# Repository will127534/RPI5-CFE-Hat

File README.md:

# CFexpress PCIe Hat for Raspberry Pi 5
Welcome to the GitHub repository for the open-source CFexpress (CFE) PCIe Hat designed specifically for the Raspberry Pi 5. This project aims to enhance the Raspberry Pi 5 by adding the ability to interface with CFexpress Type B cards directly, enabling high-speed data transfer and storage solutions.

## Features
* CFexpress Type B Card slot: Directly connect a CFexpress Type B card to your Raspberry Pi 5 for high-speed data storage and transfer.
* Automated Card Mounting: Utilizes a CH32V003 MCU for I2C to GPIO control, enabling the automated mounting and unmounting of the CFexpress card with the press of an eject button.
* QWIIC Hub: Includes a simple QWIIC hub that provides four additional QWIIC ports, allowing for easy expansion and connectivity with other QWIIC-compatible devices.
* Flexible Mounting Options: Designed to be mounted either on the top or the bottom of the Raspberry Pi 5. When mounted on top, the I2C connection is made directly from the GPIO header on the Raspberry Pi 5. For bottom mounting, the QWIIC port is used to connect and enable the auto-mount script.

## Notes
* Automounting feature requires I2C connection from either QWIIC port or RPI GPIO
* The board does not support hot-unplug even with the auto-mount script, so you will need to press the eject button to signal unmount request
* Gerber and CPL file for JLCPCB is under /Gerber
* [Interactive BOM](https://htmlpreview.github.io/?https://github.com/will127534/RPI5-CFE-Hat/blob/main/bom/ibom.html) [(provided by InteractiveHtmlBom)
](https://github.com/openscopeproject/InteractiveHtmlBom) and JLCPCB BOM under /bom
* Source Code for CH32V003 based I2C to GPIO and Python code on RPI under /software
* Limited amount on [Tindle](https://www.tindie.com/products/34094/) for sell

## Support
For questions, issues, or suggestions, please open an issue in the [GitHub repository](https://github.com/will127534/RPI5-CFE-Hat/issues)  
Also see [Quick Start Guide](https://github.com/will127534/RPI5-CFE-Hat/wiki/RPI5-CFE-Hat-Quick-Start-Guide)

## License
This project is licensed under the MIT License - see the LICENSE file for details.

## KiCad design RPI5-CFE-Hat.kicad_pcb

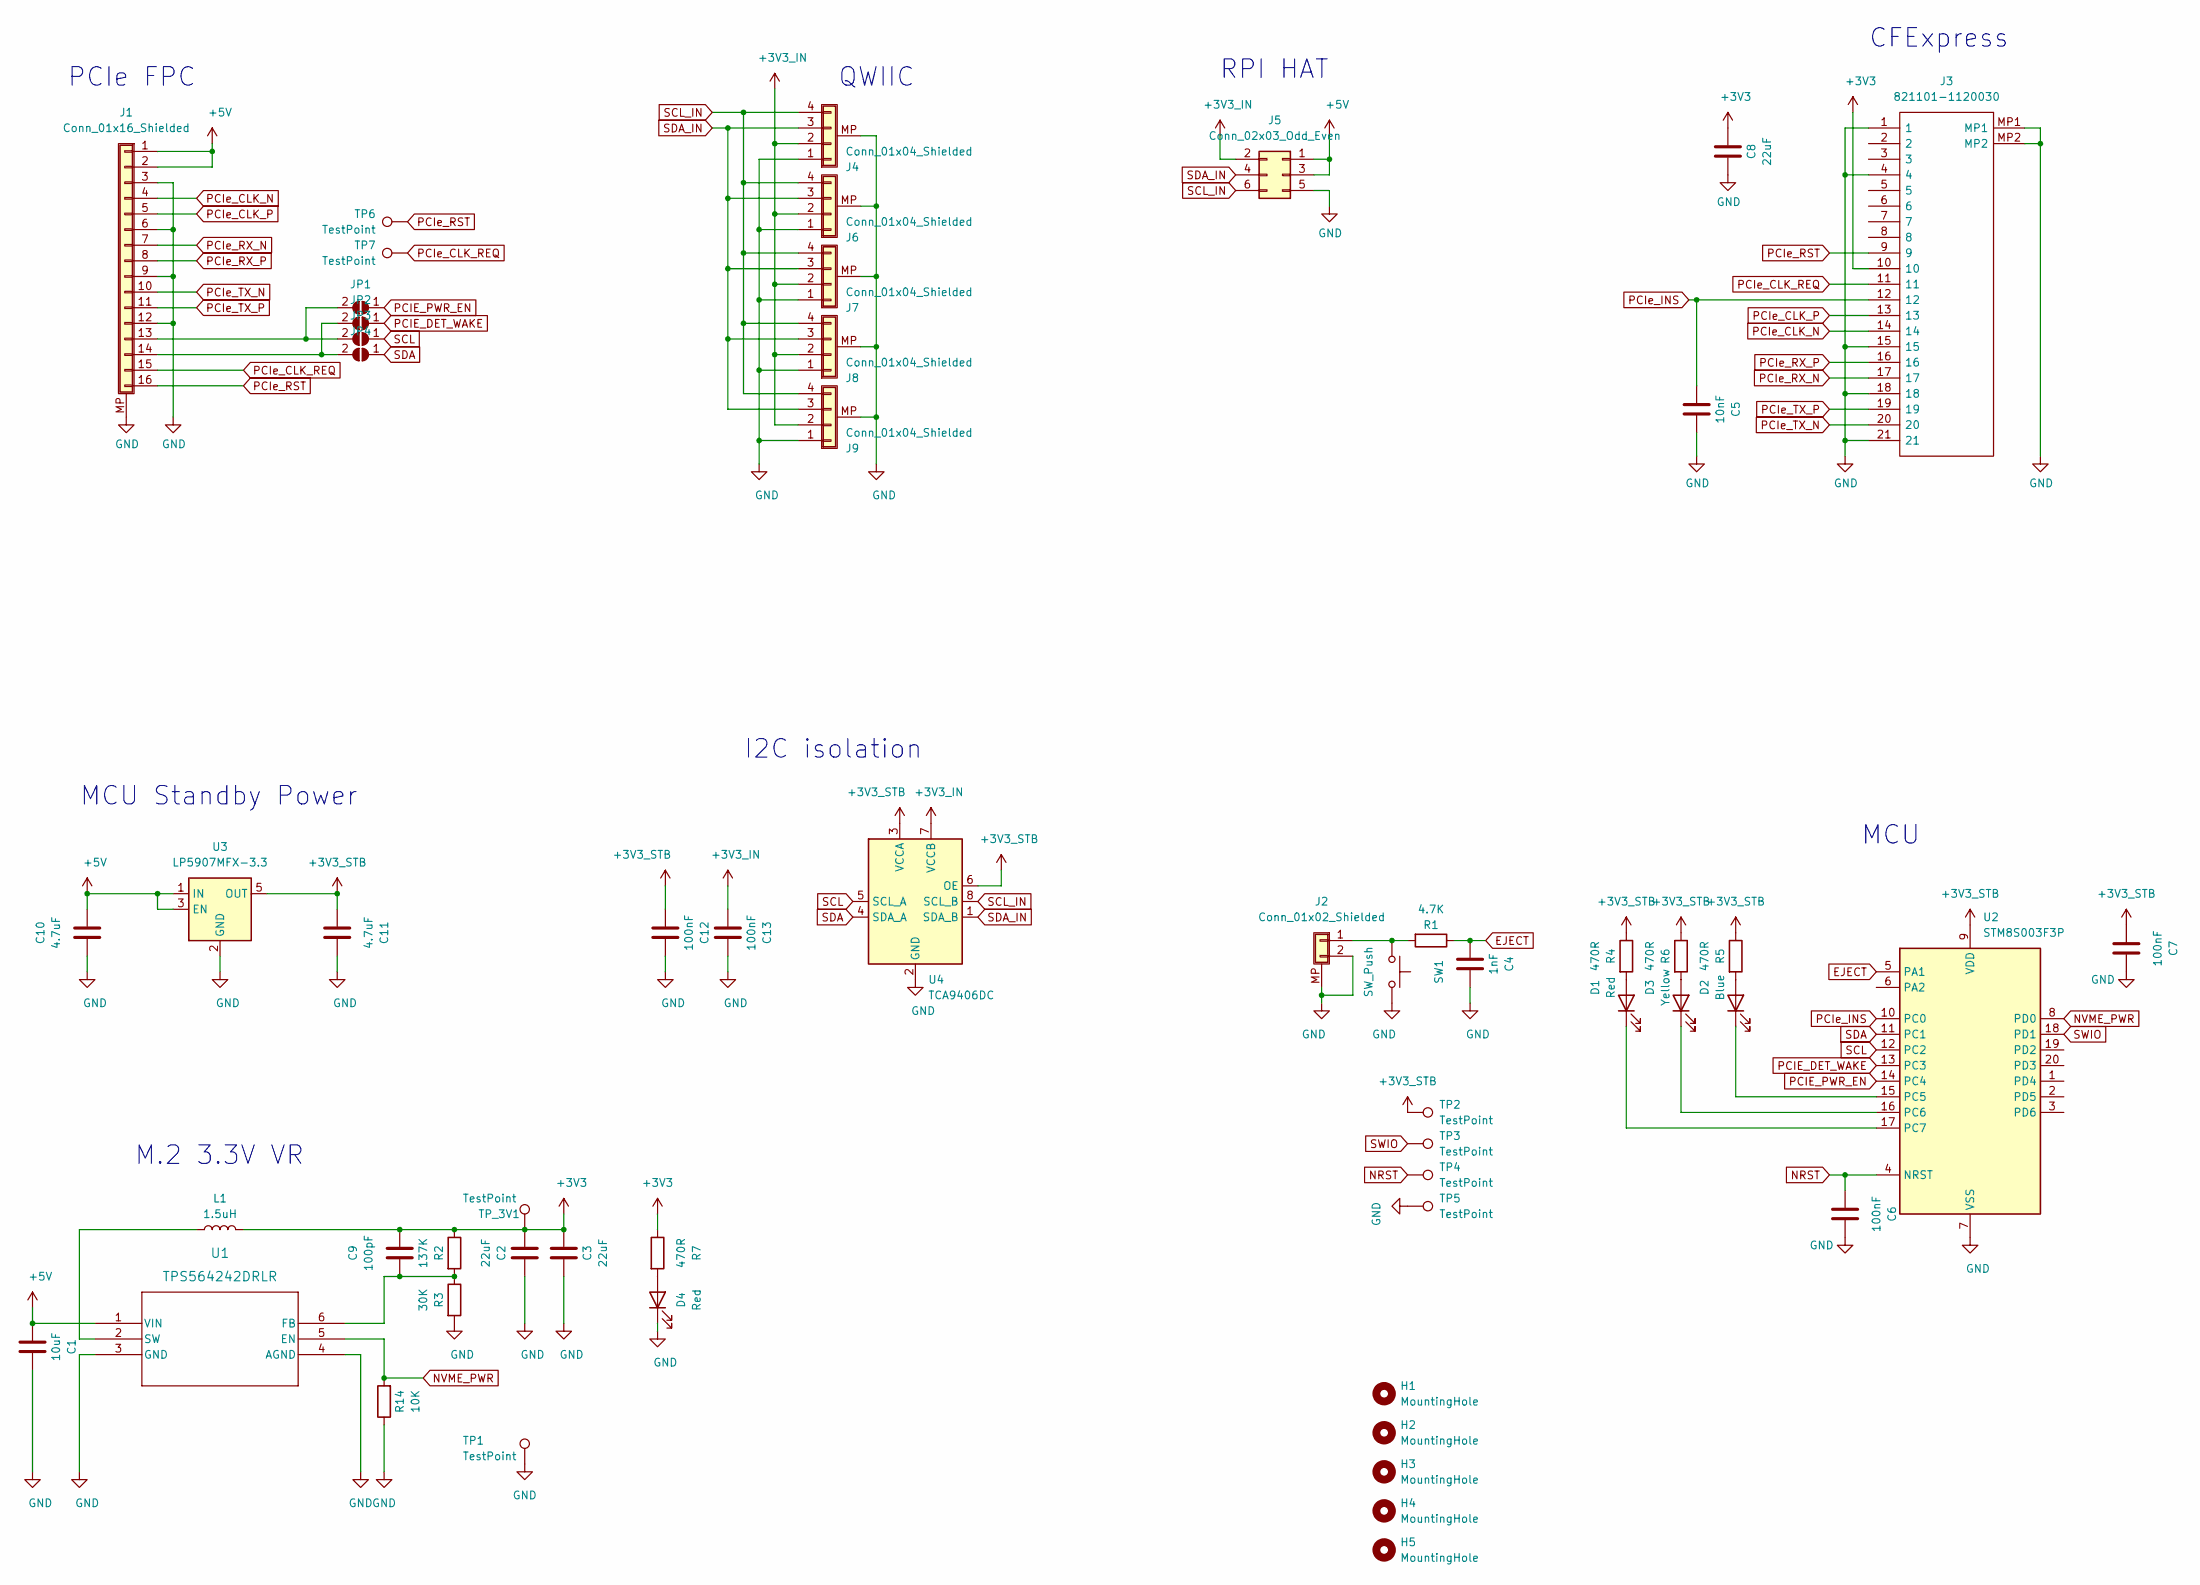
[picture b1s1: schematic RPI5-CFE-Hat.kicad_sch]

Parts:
C1: 10uF; C_0805_2012Metric
C2, C3, C8: 22uF; C_0805_2012Metric
C4: 1nF; C_0402_1005Metric
C5: 10nF; C_0402_1005Metric
C6, C7, C12, C13: 100nF; C_0402_1005Metric
C9: 100pF; C_0402_1005Metric
C10, C11: 4.7uF; C_0603_1608Metric
D1, D4: Red; LED_0603_1608Metric
D2: Blue; LED_0603_1608Metric
D3: Yellow; LED_0603_1608Metric
H1, H2, H3, H4, H5: MountingHole; MountingHole_2.7mm_M2.5
J1: Conn_01x16_Shielded; Hirose_FH12-16S-0.5SH_1x16-1MP_P0.50mm_Horizontal
J2: Conn_01x02_Shielded; JST_SH_SM02B-SRSS-TB_1x02-1MP_P1.00mm_Horizontal
J3: 821101-1120030; 8211011120030; Manufacturer_Part_Number 821101-1120030
J4, J6, J7, J8, J9: Conn_01x04_Shielded; JST_SH_SM04B-SRSS-TB_1x04-1MP_P1.00mm_Horizontal
J5: Conn_02x03_Odd_Even; PinSocket_2x03_P2.54mm_Vertical
JP1, JP2, JP3, JP4: SolderJumper_2_Open; SolderJumper-2_P1.3mm_Open_Pad1.0x1.5mm
L1: 1.5uH; L_Vishay_IHLP-2020
R1: 4.7K; R_0402_1005Metric
R2: 137K; R_0402_1005Metric
R3: 30K; R_0402_1005Metric
R4, R5, R6, R7: 470R; R_0402_1005Metric
R14: 10K; R_0402_1005Metric
SW1: SW_Push; Panasonic_EVQPUM_EVQPUD
TP1, TP2, TP3, TP4, TP5, TP6, TP7: TestPoint; TestPoint_Pad_D1.0mm
TP_3V1: TestPoint; TestPoint_Pad_D1.0mm
U1: TPS564242DRLR; TPS564242DRLR_TEX
U2: STM8S003F3P; TSSOP-20_4.4x6.5mm_P0.65mm
U3: LP5907MFX-3.3; SOT-23-5
U4: TCA9406DC; TCA9406DCUR

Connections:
+3V3: C2.1, C3.2, C8.2, C9.2, J3.10, L1.2, R2.1, R7.1, TP_3V1.1
+3V3_IN: C13.1, J4.2, J5.2, J6.2, J7.2, J8.2, J9.2, U4.7 (VCCB)
+3V3_STB: C7.1, C11.1, C12.1, R4.1, R5.1, R6.1, TP2.1, U2.9 (VDD), U3.5 (OUT), U4.3 (VCCA), U4.6 (OE)
+5V: C1.1, C10.2, J1.1, J1.2, J5.1, J5.3, U1.1 (VIN), U3.1 (IN), U3.3 (EN)
EJECT: C4.1, R1.1, U2.5 (PA1)
GND: C1.2, C2.2, C3.1, C4.2, C5.2, C6.2, C7.2, C8.1, C10.1, C11.2, C12.2, C13.2, D4.1 (K), J1.3, J1.6, J1.9, J1.12, J1.MP (Shield), J2.2, J2.MP (Shield), J3.1, J3.4, J3.15, J3.18, J3.21, J3.MP1, J3.MP2, J4.1, J4.MP (Shield), J5.5, J6.1, J6.MP (Shield), J7.1, J7.MP (Shield), J8.1, J8.MP (Shield), J9.1, J9.MP (Shield), R3.2, R14.1, SW1.1, TP1.1, TP5.1, U1.3 (GND), U1.4 (AGND), U2.7 (VSS), U3.2 (GND), U4.2 (GND)
NRST: C6.1, TP4.1, U2.4 (NRST)
NVME_PWR: R14.2, U1.5 (EN), U2.8 (PD0)
unnamed: C9.1, R2.2, R3.1, U1.6 (FB)
unnamed: D1.1 (K), U2.17 (PC7)
unnamed: D1.2 (A), R4.2
unnamed: D2.1 (K), U2.15 (PC5)
unnamed: D2.2 (A), R5.2
unnamed: D3.1 (K), U2.16 (PC6)
unnamed: D3.2 (A), R6.2
unnamed: D4.2 (A), R7.2
unnamed: J1.13, JP1.2 (B), JP3.2 (B)
unnamed: J1.14, JP2.2 (B), JP4.2 (B)
unnamed: J2.1, R1.2, SW1.2
unnamed: L1.1, U1.2 (SW)
PCIE_DET_WAKE: JP2.1 (A), U2.13 (PC3)
PCIE_PWR_EN: JP1.1 (A), U2.14 (PC4)
PCIe_CLK_N: J1.4, J3.14
PCIe_CLK_P: J1.5, J3.13
PCIe_CLK_REQ: J1.15, J3.11, TP7.1
PCIe_INS: C5.1, J3.12, U2.10 (PC0)
PCIe_RST: J1.16, J3.9, TP6.1
PCIe_RX_N: J1.7, J3.17
PCIe_RX_P: J1.8, J3.16
PCIe_TX_N: J1.10, J3.20
PCIe_TX_P: J1.11, J3.19
SCL: JP3.1 (A), U2.12 (PC2), U4.5 (SCL_A)
SCL_IN: J4.4, J5.6, J6.4, J7.4, J8.4, J9.4, U4.8 (SCL_B)
SDA: JP4.1 (A), U2.11 (PC1), U4.4 (SDA_A)
SDA_IN: J4.3, J5.4, J6.3, J7.3, J8.3, J9.3, U4.1 (SDA_B)
SWIO: TP3.1, U2.18 (PD1)

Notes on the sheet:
MCU
PCIe FPC
MCU Standby Power
QWIIC
I2C isolation
CFExpress
M.2 3.3V VR
RPI HAT

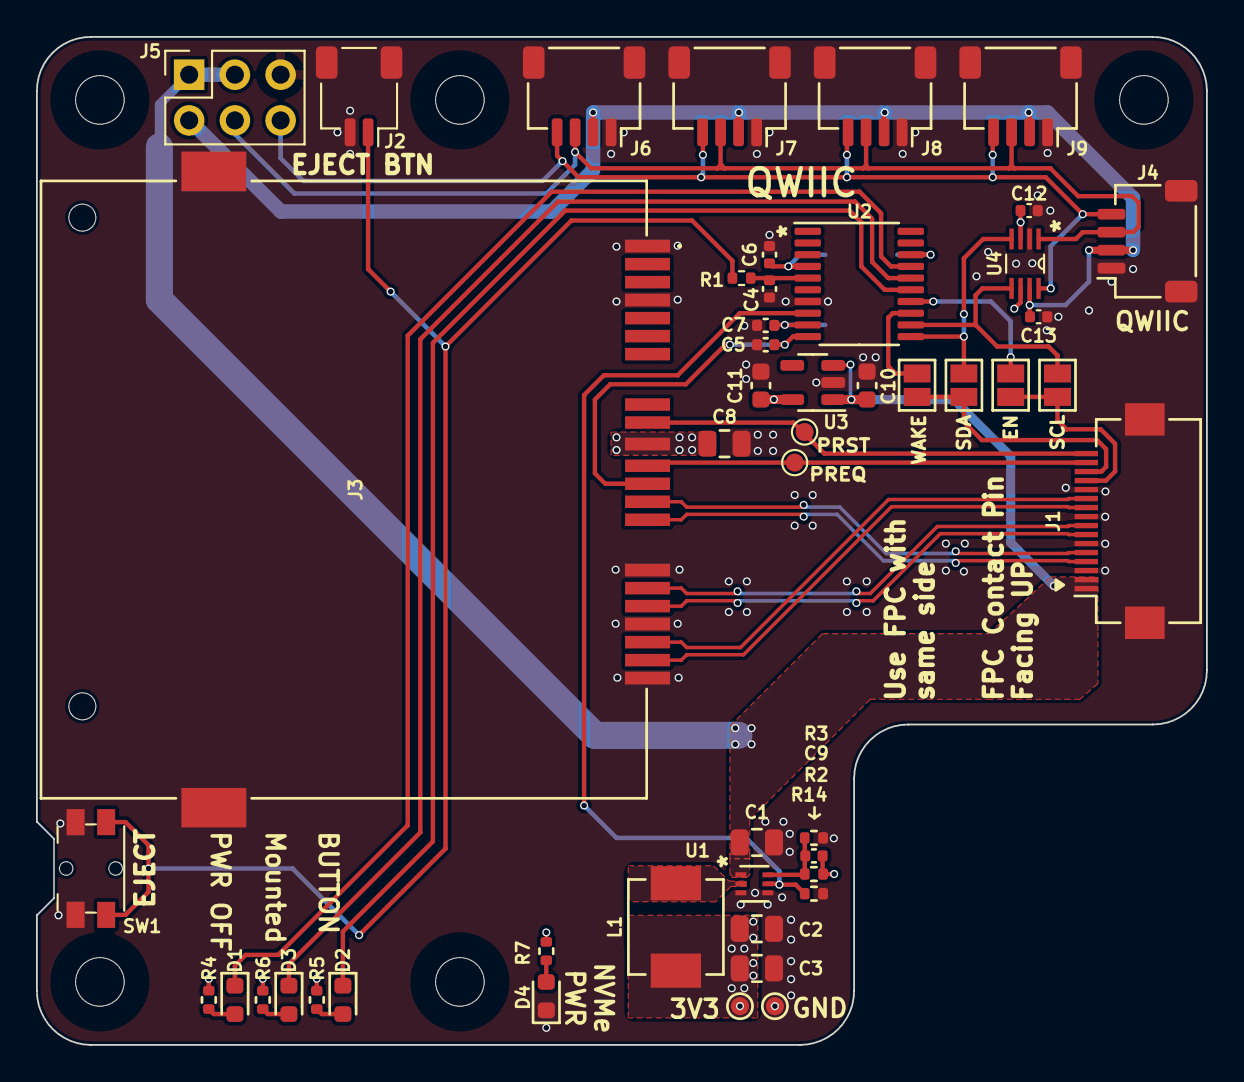
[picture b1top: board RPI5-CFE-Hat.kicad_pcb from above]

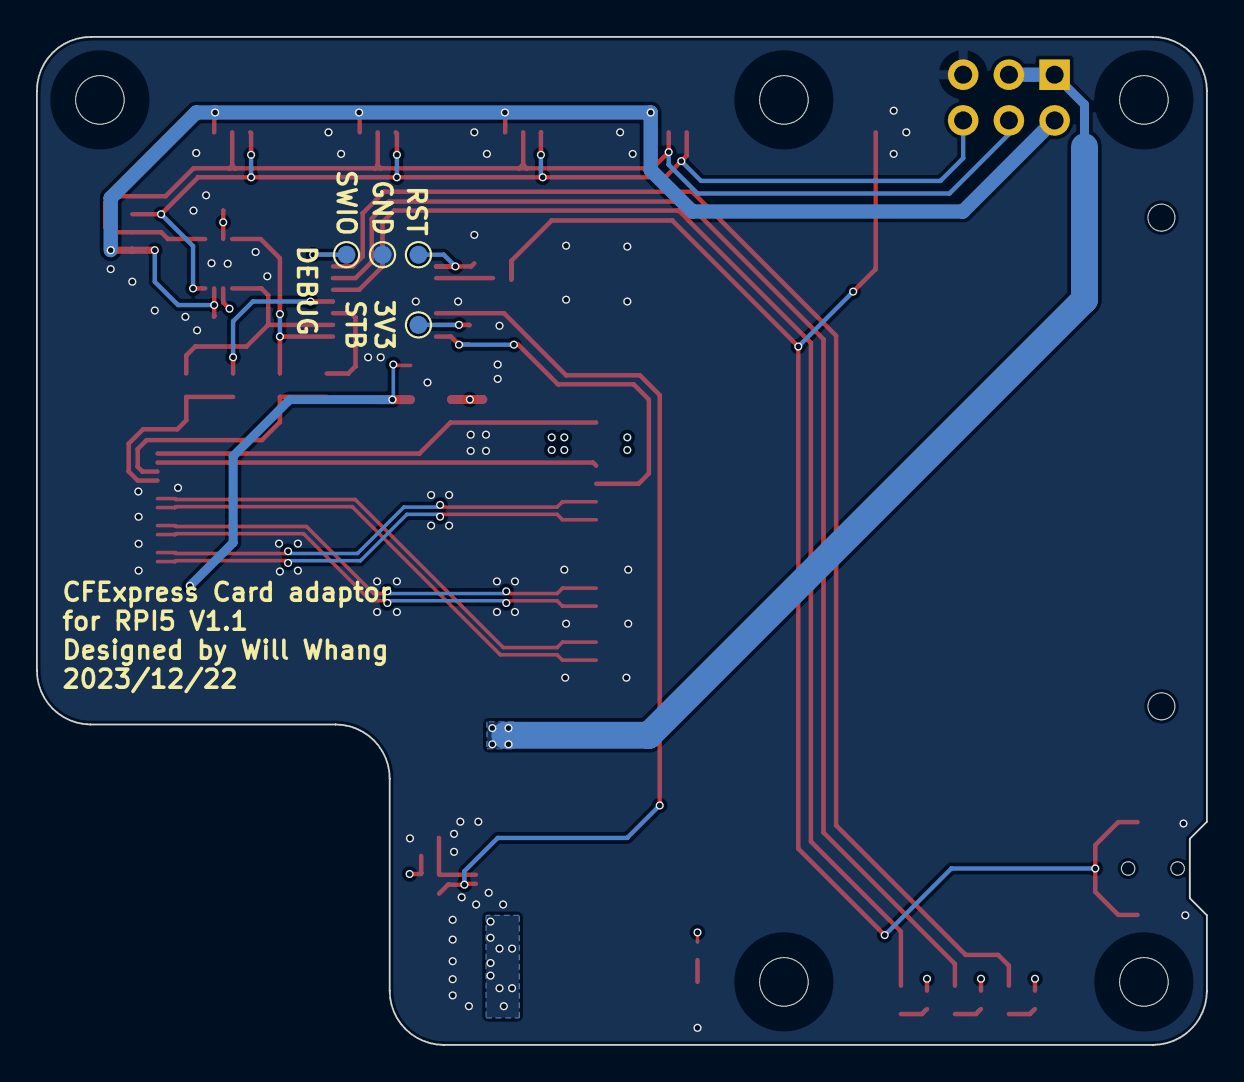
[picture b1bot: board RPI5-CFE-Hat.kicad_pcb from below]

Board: 4 copper layers, 65.0 x 56.0 mm, 57 parts (4 on the bottom side), 36 nets.

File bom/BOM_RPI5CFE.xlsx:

Comment | Designator | Footprint | JLCPCB Part #（optional）
10uF | C1 | C_0805_2012Metric | C1952587
4.7uF | C11,C10 | C_0603_1608Metric | C389010
1nF | C4 | C_0402_1005Metric | C1523
10nF | C5 | C_0402_1005Metric | C15195
100nF | C6,C13,C7,C12 | C_0402_1005Metric | C131394
22uF | C8,C3,C2 | C_0805_2012Metric | C907991
100pF | C9 | C_0402_1005Metric | C445763
Blue | D2 | LED_0603_1608Metric | C72041
Yellow | D3 | LED_0603_1608Metric | C72038
Red | D4,D1 | LED_0603_1608Metric | C128249
Conn_01x16_Shielded | J1 | Hirose_FH12A-16S-0.5SH_1x16-1MP_P0.50mm_Horizontal | C597996
Conn_01x02_Shielded | J2 | JST_SH_SM02B-SRSS-TB_1x02-1MP_P1.00mm_Horizontal | C160402
101M-TE10 | J3 | 101M-TE10 | C17611134
Conn_01x04_Shielded | J9,J6,J7,J8,J4 | JST_SH_SM04B-SRSS-TB_1x04-1MP_P1.00mm_Horizontal | C160404
1.5uH | L1 | L_Vishay_IHLP-2020 | C845007
4.7K | R1 | R_0402_1005Metric | C140158
10K | R14 | R_0402_1005Metric | C144807
137K | R2 | R_0402_1005Metric | C102804
30K | R3 | R_0402_1005Metric | C352437
470R | R7,R6,R4,R5 | R_0402_1005Metric | C25117
SW_Push | SW1 | Panasonic_EVQPUM_EVQPUD | C388886
TPS564242DRLR | U1 | TPS564242DRLR_TEX | C5219267
CH32V003F4P6 | U2 | TSSOP-20_4.4x6.5mm_P0.65mm | C5187096
LP5907MFX-3.3 | U3 | SOT-23-5 | C80670
TCA9406DC | U4 | TCA9406DCUR | C840107

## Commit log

2024-03-24 init
2024-03-24 Adding CH32v003 code and script
2024-03-24 Add images
2025-02-18 Fixing compatiable issue on 16GB RPI5
